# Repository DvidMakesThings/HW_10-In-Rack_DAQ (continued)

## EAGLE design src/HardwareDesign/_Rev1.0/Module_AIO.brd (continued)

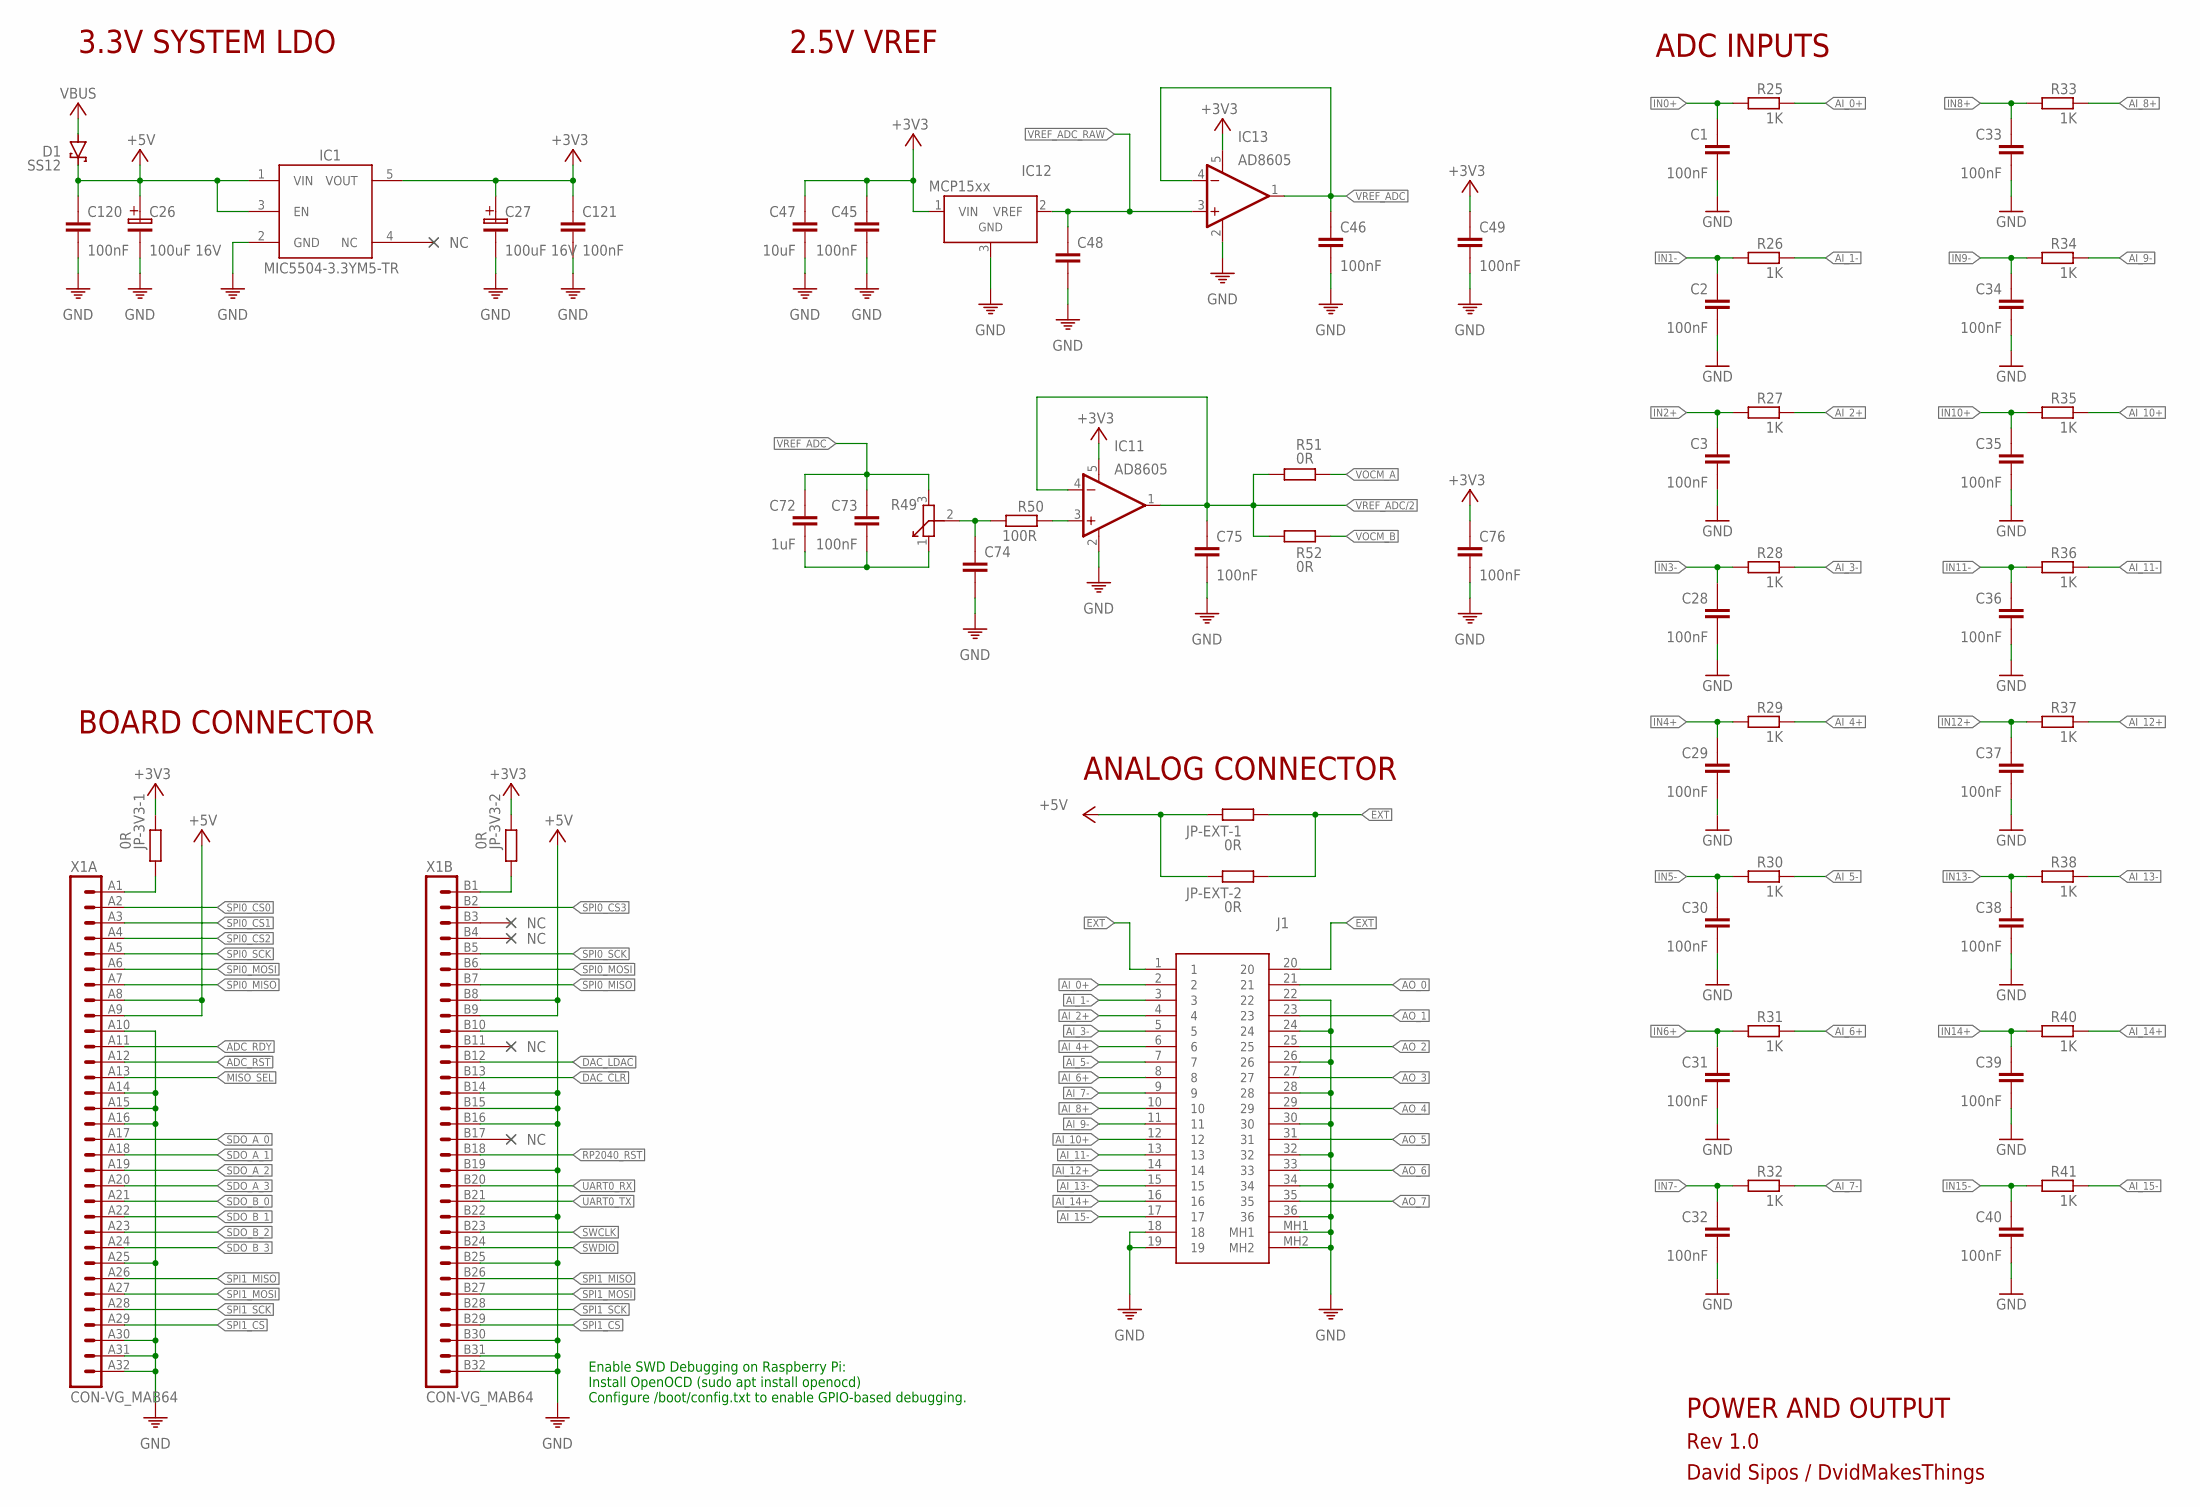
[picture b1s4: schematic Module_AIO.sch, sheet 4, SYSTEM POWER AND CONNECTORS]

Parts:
C1, C2, C3, C28, C29, C30, C31, C32, C33, C34, C35, C36, C37, C38, C39, C40, C45, C46, C49, C73, C75, C76, C120, C121: 100nF; C0402
C26, C27: 100uF 16V; 100UF-16V
C47: 10uF; C0402
C48, C74: C-0402; C0402
C72: 1uF; C0402
D1: SS12; SMA
IC1: MIC5504-3.3YM5-TR; SOT23-5
IC11, IC13: AD8605; SOT23-5
IC12: MCP1525T-I/TT; SOT23
J1: N10236-52B3PC; MDB36
JP-3V3-1, JP-3V3-2: 0R; 0603
JP-EXT-1, JP-EXT-2: 0R; 0603
R25, R26, R27, R28, R29, R30, R31, R32, R33, R34, R35, R36, R37, R38, R40, R41: 1K; 0402
R49: R-TRIM; TC33X
R50: 100R; 0402
R51, R52: 0R; 0603
X1: CON-VG_MAB64

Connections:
!ADC_RST: X1.A12 (12); also elsewhere on the board
+3V3: C27.1, C45.1, C47.1, C49.1, C76.1, C121.1, IC1.5 (VOUT), IC11.5 (V+), IC12.1 (VIN), IC13.5 (V+), JP-3V3-1.1, JP-3V3-2.1; also elsewhere on the board
+5V: C26.1, C120.1, D1.C, IC1.1 (VIN), IC1.3 (EN), JP-EXT-1.1, JP-EXT-2.1, X1.A8 (8), X1.A9 (9), X1.B8 (8), X1.B9 (9); also elsewhere on the board
ADC_RDY: X1.A11 (11); also elsewhere on the board
AI_0+: J1.2, R25.1
AI_1-: J1.3, R26.1
AI_2+: J1.4, R27.1
AI_3-: J1.5, R28.1
AI_4+: J1.6, R29.1
AI_5-: J1.7, R30.1
AI_6+: J1.8, R31.1
AI_7-: J1.9, R32.1
AI_8+: J1.10, R33.1
AI_9-: J1.11, R34.1
AI_10+: J1.12, R35.1
AI_11-: J1.13, R36.1
AI_12+: J1.14, R37.1
AI_13-: J1.15, R38.1
AI_14+: J1.16, R40.1
AI_15-: J1.17, R41.1
AO_0: J1.21; also elsewhere on the board
AO_1: J1.23; also elsewhere on the board
AO_2: J1.25; also elsewhere on the board
AO_3: J1.27; also elsewhere on the board
AO_4: J1.29; also elsewhere on the board
AO_5: J1.31; also elsewhere on the board
AO_6: J1.33; also elsewhere on the board
AO_7: J1.35; also elsewhere on the board
DAC_!CLR: X1.B13 (13); also elsewhere on the board
DAC_!LDAC: X1.B12 (12); also elsewhere on the board
EXT: J1.1, J1.20, JP-EXT-1.2, JP-EXT-2.2
GND: C1.2, C2.2, C3.2, C26.2, C27.2, C28.2, C29.2, C30.2, C31.2, C32.2, C33.2, C34.2, C35.2, C36.2, C37.2, C38.2, C39.2, C40.2, C45.2, C46.2, C47.2, C48.2, C49.2, C74.2, C75.2, C76.2, C120.2, C121.2, IC1.2 (GND), IC11.2 (V-), IC12.3 (GND), IC13.2 (V-), J1.18, J1.19, J1.22, J1.24, J1.26, J1.28, J1.30, J1.32, J1.34, J1.36, J1.MH1, J1.MH2, X1.A10 (10), X1.A14 (14), X1.A15 (15), X1.A16 (16), X1.A25 (25), X1.A30 (30), X1.A31 (31), X1.A32 (32), X1.B10 (10), X1.B14 (14), X1.B15 (15), X1.B16 (16), X1.B19 (19), X1.B22 (22), X1.B25 (25), X1.B30 (30), X1.B31 (31), X1.B32 (32); also elsewhere on the board
IN0+: C1.1, R25.2; also elsewhere on the board
IN1-: C2.1, R26.2; also elsewhere on the board
IN2+: C3.1, R27.2; also elsewhere on the board
IN3-: C28.1, R28.2; also elsewhere on the board
IN4+: C29.1, R29.2; also elsewhere on the board
IN5-: C30.1, R30.2; also elsewhere on the board
IN6+: C31.1, R31.2; also elsewhere on the board
IN7-: C32.1, R32.2; also elsewhere on the board
IN8+: C33.1, R33.2; also elsewhere on the board
IN9-: C34.1, R34.2; also elsewhere on the board
IN10+: C35.1, R35.2; also elsewhere on the board
IN11-: C36.1, R36.2; also elsewhere on the board
IN12+: C37.1, R37.2; also elsewhere on the board
IN13-: C38.1, R38.2; also elsewhere on the board
IN14+: C39.1, R40.2; also elsewhere on the board
IN15-: C40.1, R41.2; also elsewhere on the board
MISO_SEL: X1.A13 (13); also elsewhere on the board
unnamed: JP-3V3-1.2, X1.A1 (1)
unnamed: JP-3V3-2.2, X1.B1 (1)
unnamed: C72.2, C73.2, R49.1
unnamed: C74.1, R49.2, R50.1
unnamed: IC11.3 (+IN), R50.2
RP2040_RST: X1.B18 (18); also elsewhere on the board
SDO_A_0: X1.A17 (17); also elsewhere on the board
SDO_A_1: X1.A18 (18); also elsewhere on the board
SDO_A_2: X1.A19 (19); also elsewhere on the board
SDO_A_3: X1.A20 (20); also elsewhere on the board
SDO_B_0: X1.A21 (21); also elsewhere on the board
SDO_B_1: X1.A22 (22); also elsewhere on the board
SDO_B_2: X1.A23 (23); also elsewhere on the board
SDO_B_3: X1.A24 (24); also elsewhere on the board
SPI0_CS0: X1.A2 (2); also elsewhere on the board
SPI0_CS1: X1.A3 (3); also elsewhere on the board
SPI0_CS2: X1.A4 (4); also elsewhere on the board
SPI0_CS3: X1.B2 (2); also elsewhere on the board
SPI0_MISO: X1.A7 (7), X1.B7 (7); also elsewhere on the board
SPI0_MOSI: X1.A6 (6), X1.B6 (6); also elsewhere on the board
SPI0_SCK: X1.A5 (5), X1.B5 (5); also elsewhere on the board
SPI1_CS: X1.A29 (29), X1.B29 (29); also elsewhere on the board
SPI1_MISO: X1.A26 (26), X1.B26 (26); also elsewhere on the board
SPI1_MOSI: X1.A27 (27), X1.B27 (27); also elsewhere on the board
SPI1_SCK: X1.A28 (28), X1.B28 (28); also elsewhere on the board
SWCLK: X1.B23 (23); also elsewhere on the board
SWDIO: X1.B24 (24); also elsewhere on the board
UART0_RX: X1.B20 (20); also elsewhere on the board
UART0_TX: X1.B21 (21); also elsewhere on the board
VBUS: D1.A; also elsewhere on the board
VOCM_A: R51.2; also elsewhere on the board
VOCM_B: R52.1; also elsewhere on the board
VREF_ADC: C46.1, C72.1, C73.1, IC13.1 (OUT), IC13.4 (-IN), R49.3; also elsewhere on the board
VREF_ADC/2: C75.1, IC11.1 (OUT), IC11.4 (-IN), R51.1, R52.2; also elsewhere on the board
VREF_ADC_RAW: C48.1, IC12.2 (VREF), IC13.3 (+IN); also elsewhere on the board

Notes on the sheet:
3.3V SYSTEM LDO
2.5V VREF
ADC INPUTS
Enable SWD Debugging on Raspberry Pi: Install OpenOCD (sudo apt install openocd) Configure /boot/config.txt to enable GPIO-based debugging.
BOARD CONNECTOR
ANALOG CONNECTOR
POWER AND OUTPUT
Rev 1.0
David Sipos / DvidMakesThings

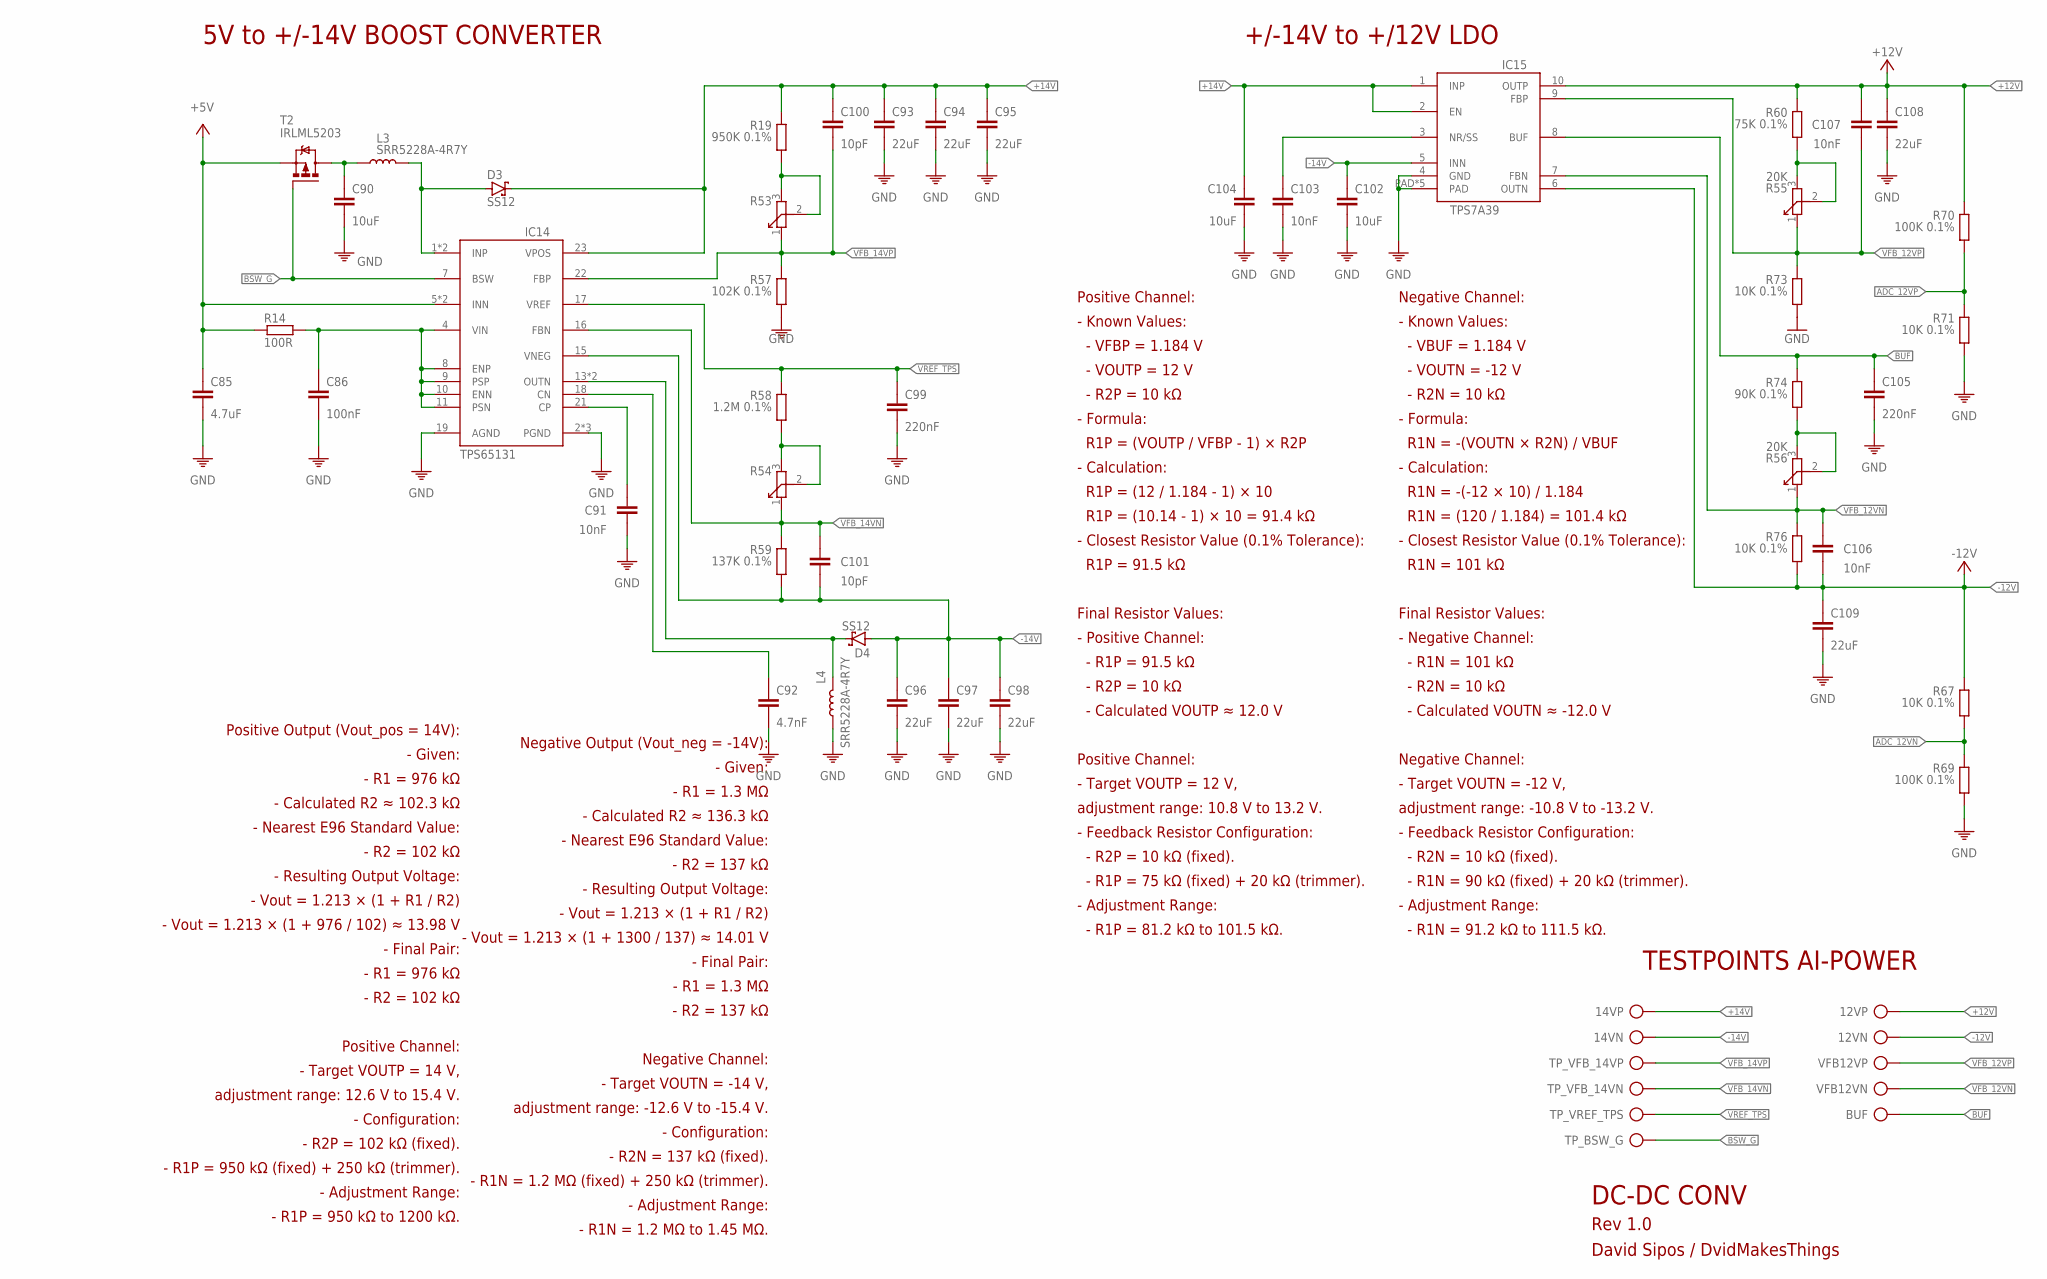
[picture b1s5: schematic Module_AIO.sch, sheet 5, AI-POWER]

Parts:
12VN, 12VP, 14VN, 14VP: TP
BUF: TP
C85: 4.7uF; C0402
C86: 100nF; C0402
C90: 10uF; C0402
C91, C103, C106, C107: 10nF; C0402
C92: 4.7nF; C0402
C93, C94, C95, C96, C97, C98, C108, C109: 22uF; C0805
C99, C105: 220nF; C0402
C100, C101: 10pF; C0402
C102, C104: 10uF; C0805
D3, D4: SS12; SMA
IC14: TPS65131; VQFN24-4X4-THERMAL2.5X2.5
IC15: TPS7A39; WSON10-3X3
L3, L4: SRR5228A-4R7Y; SRR5228A
R14: 100R; 1206
R19: 950K 0.1%; 0402
R53, R54: R-TRIM; TC33X
R55, R56: 20K; TC33X
R57: 102K 0.1%; 0402
R58: 1.2M 0.1%; 0402
R59: 137K 0.1%; 0402
R60: 75K 0.1%; 0402
R67, R71, R73, R76: 10K 0.1%; 0402
R69, R70: 100K 0.1%; 0402
R74: 90K 0.1%; 0402
T2: IRLML5203; MICRO3
TP_BSW_G: TP
TP_VFB_14VN, TP_VFB_14VP: TP
TP_VREF_TPS: TP
VFB12VN, VFB12VP: TP

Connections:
+5V: C85.1, IC14.5 (INN), IC14.6 (INN), R14.2, T2.2 (S); also elsewhere on the board
+12V: 12VP.TP, C107.2, C108.1, IC15.10 (OUTP), R60.1, R70.1; also elsewhere on the board
+14V: 14VP.TP, C93.1, C94.1, C95.1, C100.1, C104.1, D3.C, IC14.23 (VPOS), IC15.1 (INP), IC15.2 (EN), R19.1
-12V: 12VN.TP, C106.1, C109.1, IC15.6 (OUTN), R67.1, R76.2; also elsewhere on the board
-14V: 14VN.TP, C96.1, C97.1, C98.1, C101.1, C102.1, D4.A, IC14.15 (VNEG), IC15.5 (INN), R59.2
ADC_12VN: R67.2, R69.1; also elsewhere on the board
ADC_12VP: R70.2, R71.1; also elsewhere on the board
BSW_G: IC14.7 (BSW), T2.1 (G), TP_BSW_G.TP
BUF: BUF.TP, C105.2, IC15.8 (BUF), R74.1
GND: C85.2, C86.2, C90.2, C91.2, C92.2, C93.2, C94.2, C95.2, C96.2, C97.2, C98.2, C99.1, C102.2, C103.2, C104.2, C105.1, C108.2, C109.2, IC14.2 (PGND), IC14.3 (PGND), IC14.19 (AGND), IC14.25 (PGND), IC15.4 (GND), IC15.PAD, IC15.PAD1 (PAD), IC15.PAD2 (PAD), IC15.PAD3 (PAD), IC15.PAD4 (PAD), L4.1, R57.2, R69.2, R71.2, R73.2; also elsewhere on the board
unnamed: D3.A, IC14.1 (INP), IC14.24 (INP), L3.2
unnamed: C90.1, L3.1, T2.3 (D)
unnamed: C86.1, IC14.4 (VIN), IC14.8 (ENP), IC14.9 (PSP), IC14.10 (ENN), IC14.11 (PSN), R14.1
unnamed: C91.1, IC14.21 (CP)
unnamed: C92.1, IC14.18 (CN)
unnamed: D4.C, IC14.13 (OUTN), IC14.14 (OUTN), L4.2
unnamed: R55.2, R55.3, R60.2
unnamed: C103.1, IC15.3 (NR/SS)
unnamed: R56.2, R56.3, R74.2
unnamed: R19.2, R53.2, R53.3
unnamed: R54.2, R54.3, R58.2
VFB_12VN: C106.2, IC15.7 (FBN), R56.1, R76.1, VFB12VN.TP
VFB_12VP: C107.1, IC15.9 (FBP), R55.1, R73.1, VFB12VP.TP
VFB_14VN: C101.2, IC14.16 (FBN), R54.1, R59.1, TP_VFB_14VN.TP
VFB_14VP: C100.2, IC14.22 (FBP), R53.1, R57.1, TP_VFB_14VP.TP
VREF_TPS: C99.2, IC14.17 (VREF), R58.1, TP_VREF_TPS.TP

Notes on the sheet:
5V to +/-14V BOOST CONVERTER
Positive Output (Vout_pos = 14V): - Given: - R1 = 976 kΩ - Calculated R2 ≈ 102.3 kΩ - Nearest E96 Standard Value: - R2 = 102 kΩ - Resulting Output Voltage: - Vout = 1.213 × (1 + R1 / R2) - Vout = 1.213 × (1 + 976 / 102) ≈ 13.98 V - Final Pair: - R1 = 976 kΩ - R2 = 102 kΩ Positive Channel: - Target 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
Negative Output (Vout_neg = -14V): - Given: - R1 = 1.3 MΩ - Calculated R2 ≈ 136.3 kΩ - Nearest E96 Standard Value: - R2 = 137 kΩ - Resulting Output Voltage: - Vout = 1.213 × (1 + R1 / R2) - Vout = 1.213 × (1 + 1300 / 137) ≈ 14.01 V - Final Pair: - R1 = 1.3 MΩ - R2 = 137 kΩ Negative Channel: - Targe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
Positive Channel: - Known Values: - VFBP = 1.184 V - VOUTP = 12 V - R2P = 10 kΩ - Formula: R1P = (VOUTP / VFBP - 1) × R2P - Calculation: R1P = (12 / 1.184 - 1) × 10 R1P = (10.14 - 1) × 10 = 91.4 kΩ - Closest Resistor Value (0.1% Tolerance): R1P = 91.5 kΩ Final Resistor Values: - Positive Channel: -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
Negative Channel: - Known Values: - VBUF = 1.184 V - VOUTN = -12 V - R2N = 10 kΩ - Formula: R1N = -(VOUTN × R2N) / VBUF - Calculation: R1N = -(-12 × 10) / 1.184 R1N = (120 / 1.184) = 101.4 kΩ - Closest Resistor Value (0.1% Tolerance): R1N = 101 kΩ Final Resistor Values: - Negative Channel: - R1N = 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
+/-14V to +/12V LDO
TESTPOINTS AI-POWER
DC-DC CONV
Rev 1.0
David Sipos / DvidMakesThings

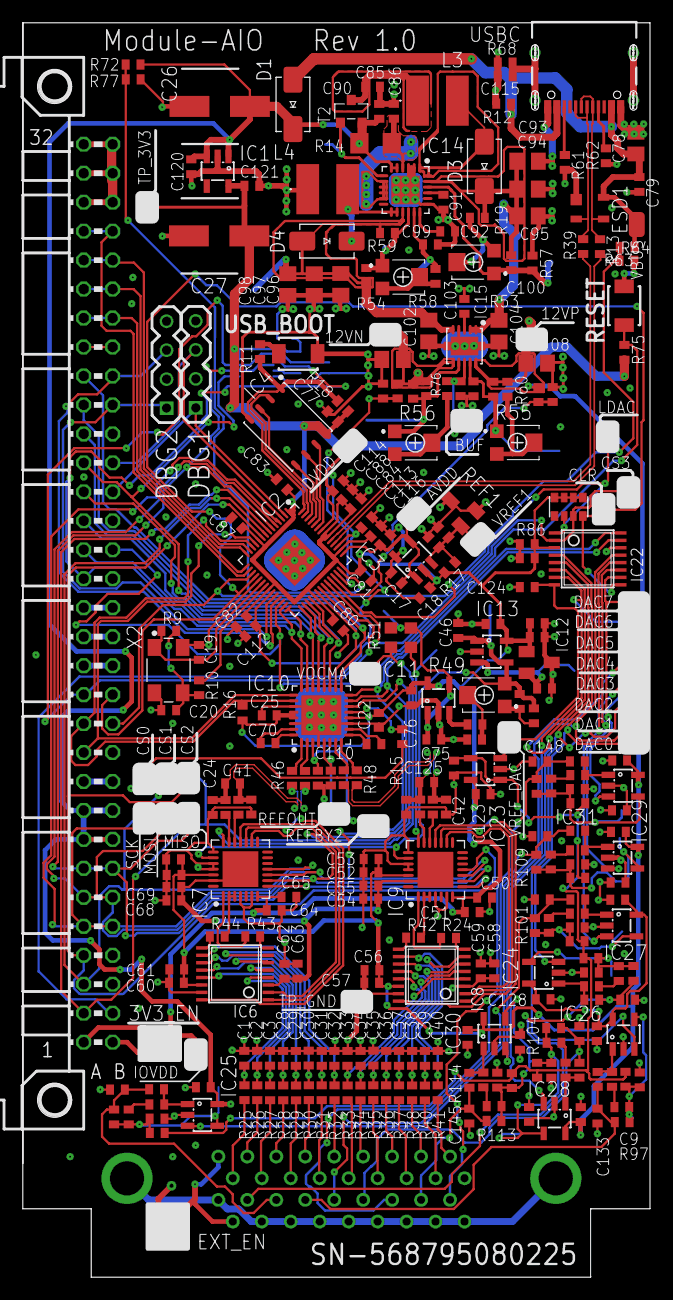
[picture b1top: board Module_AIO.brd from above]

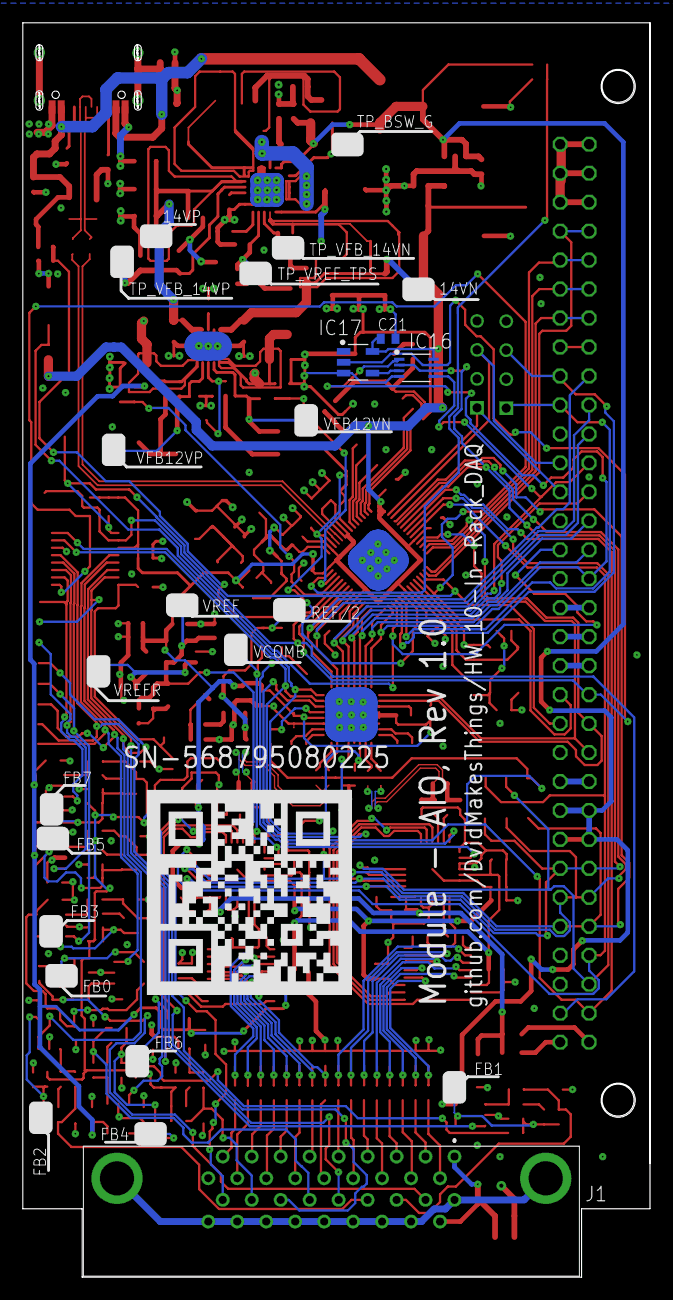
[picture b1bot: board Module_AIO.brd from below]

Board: 4 copper layers, 55.0 x 110.0 mm, 345 parts (24 on the bottom side), 198 nets.

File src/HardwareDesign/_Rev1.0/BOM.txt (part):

Partlist exported from G:/_GitHub/HW_10-In-Rack_DAQ/src/HardwareDesign/Module_AIO.sch at 27/02/2025 22:39

Part        Value             Device                 Package                   Description                                                                                                                                                                          APPLICATION CREATED_BY    DATASHEET-URL                                            DIGIKEY_PART_NUMBER DIGIKEY_PN     GERDER     INTERFACE-TYPE IR LABEL MANUFACTURER     MOUNT MPN             PACKAGE        PACKAGING     PART-NUMBER  PINS TYPE       VALUE        WORKING-VOLTAGE
12VN        TP                TP                     TP                                                                                                                                                                                                                                                                                                                                                                                                                                                                                                   
12VP        TP                TP                     TP                                                                                                                                                                                                                                                                                                                                                                                                                                                                                                   
14VN        TP                TP                     TP                                                                                                                                                                                                                                                                                                                                                                                                                                                                                                   
14VP        TP                TP                     TP                                                                                                                                                                                                                                                                                                                                                                                                                                                                                                   
AVDD        TP                TP                     TP                                                                                                                                                                                                                                                                                                                                                                                                                                                                                                   
BUF         TP                TP                     TP                                                                                                                                                                                                                                                                                                                                                                                                                                                                                                   
C1          100nF             C-0402                 C0402                                                                                                                                                                                                                                                                                                                                                                                                                                                                                                
C2          100nF             C-0402                 C0402                                                                                                                                                                                                                                                                                                                                                                                                                                                                                                
C3          100nF             C-0402                 C0402                                                                                                                                                                                                                                                                                                                                                                                                                                                                                                
C4          100nF             C-0402                 C0402                                                                                                                                                                                                                                                                                                                                                                                                                                                                                                
C5          100nF             C-0402                 C0402                                                                                                                                                                                                                                                                                                                                                                                                                                                                                                
C6          100nF             C-0402                 C0402                                                                                                                                                                                                                                                                                                                                                                                                                                                                                                
C7          100nF             C-0402                 C0402                                                                                                                                                                                                                                                                                                                                                                                                                                                                                                
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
